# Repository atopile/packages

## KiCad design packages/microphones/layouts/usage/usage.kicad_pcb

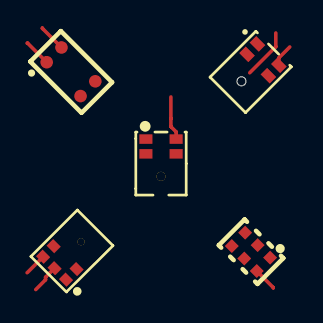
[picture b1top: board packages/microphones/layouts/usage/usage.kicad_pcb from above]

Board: 2 copper layers, 5 parts (0 on the bottom side), 7 nets.

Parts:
MIC1: MIC-SMD_5P-L3.5-W2.7-TL_MMICT390200012
U1: MIC-SMD_4P-L3.8-W2.3-P2.66-TL
U2: MIC-SMD_5P_L3.5-W2.7-P0.82_SPH0641LU4H-1
U3: MIC-SMD_6P-L3.5-W2.7-P0.90-BL
U4: MIC-SMD_6P-L2.8-W1.9-P0.98-TL

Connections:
SCK: U2.4, U3.4
SD: U2.1, U3.6
WS: U2.2, U3.1
lv: MIC1.3, U1.3, U1.4, U2.3, U3.3
microphone_pdm_1_8v-power-hv: U4.2, U4.4
microphone_pdm_1_8v-power-lv: U4.1, U4.3
microphone_pdm_3v3-reference-hv: MIC1.2, MIC1.5, U1.2, U2.5, U3.5

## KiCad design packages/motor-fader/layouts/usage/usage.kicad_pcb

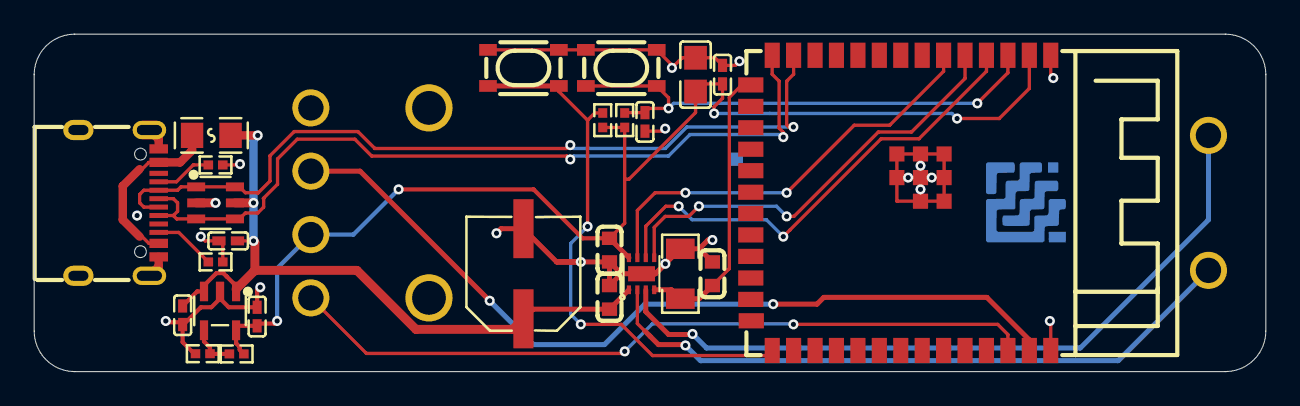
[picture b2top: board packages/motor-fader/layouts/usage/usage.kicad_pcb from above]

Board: 2 copper layers, 73.0 x 20.0 mm, 27 parts (1 on the bottom side), 19 nets.

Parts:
C1: 10µF ±10% 25V X5R; C0805
C2, C10: 100nF ±10% 16V X7R; C0402
C3: CAP-SMD_BD6.3-L6.6-W6.6-LS7.6-FD
C4, C5, C6: 1µF ±10% 25V X5R; C0402
C7, C8, C9: 100nF ±10% 50V X7R; C0603
D1: SOT-23-6_L2.9-W1.6-P0.95-LS2.8-BL
F1: F0805
LOGO1: atopile_Logo_25x6mm
R1, R3, R4: 10kΩ ±1% 62.5mW; R0402
R2: RES-ADJ-TH_RS60N11M9A0F
R5: 18kΩ ±1% 62.5mW; R0402
R6: 1Ω ±1% 250mW; R1206
R7, R8: 5.1kΩ ±1% 62.5mW; R0402
SW1, SW2: KEY-SMD_4P-L4.2-W3.2-P2.20-LS4.6
U1: WSON-8_L2.0-W2.0-P0.50-TL-EP
U2: SOT-23-5_L3.0-W1.7-P0.95-LS2.8-BL
U3: WIRELM-SMD_ESP32-S3-WROOM-1
USB1: USB-C-SMD_TYPE-C-6PIN-2MD-073

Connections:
A: R2.A, U1.3
B: R2.B, U1.2
CURRENT_SENSE: C7.1, R6.1, U1.4, U3.15
GND: C1.2, C2.2, C3.2, C4.2, C5.2, C6.2, C7.2, C8.2, C9.2, C10.2, D1.2, R2.1, R4.2, R6.2, R7.2, R8.2, SW1.1, SW1.2, SW2.1, SW2.2, U1.9, U2.2, U3.1, U3.40, U3.41, USB1.1, USB1.12, USB1.13, USB1.14, USB1.15, USB1.16
IN_N: U1.6, U3.4
IN_P: U1.5, U3.5
POT_SENSE: R2.2, U3.38
SLEEP: U1.7, U3.6
TOUCH_SENSE: R2.T, U3.39
USB_D_N: D1.1, D1.6, U3.13, USB1.5, USB1.7
USB_D_P: D1.3, D1.4, U3.14, USB1.6, USB1.8
VCC: F1.1, USB1.2, USB1.11
VCC_LOGIC: C1.1, C2.1, C6.1, C8.1, R1.1, R2.3, R3.1, R5.1, U1.8, U2.5, U3.2
VCC_MOTOR: C3.1, C5.1, C9.1, C10.1, D1.5, F1.2, U1.1, U2.1, U2.3
VDIV_OUTPUT: R4.1, R5.2, U2.4
cc[0]-line: R7.1, USB1.4
cc[1]-line: R8.1, USB1.10
enable-output: C4.1, R3.2, SW2.3, SW2.4, U3.3
io[0]-output: R1.2, SW1.3, SW1.4, U3.27

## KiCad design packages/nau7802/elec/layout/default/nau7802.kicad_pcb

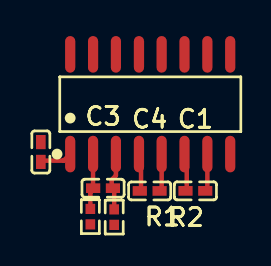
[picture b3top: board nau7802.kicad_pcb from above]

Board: 2 copper layers, 7 parts (0 on the bottom side), 7 nets.

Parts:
C1, C2, C3: 100nF ±10% 16V X7R; C0402-b3ef17
C4: 470pF ±10% 50V X7R; C0402-b3ef17
R1, R2: 47Ω ±1% 62.5mW; R0402-56259e
U1: SOP-16_L9.9-W3.9-P1.27-LS6.0-BL

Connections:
REFP: C2.1, U1.1
VBG: C1.1, U1.6
VIN1N: C3.1, R1.1, U1.2
VIN1P: C3.2, R2.1, U1.3
VIN2N: C4.1, U1.4
VIN2P: C4.2, U1.5
gnd: C1.2, C2.2, U1.7, U1.8, U1.9
